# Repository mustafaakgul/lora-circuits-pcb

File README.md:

## Collection of LoRa peripheral circuits for various applications

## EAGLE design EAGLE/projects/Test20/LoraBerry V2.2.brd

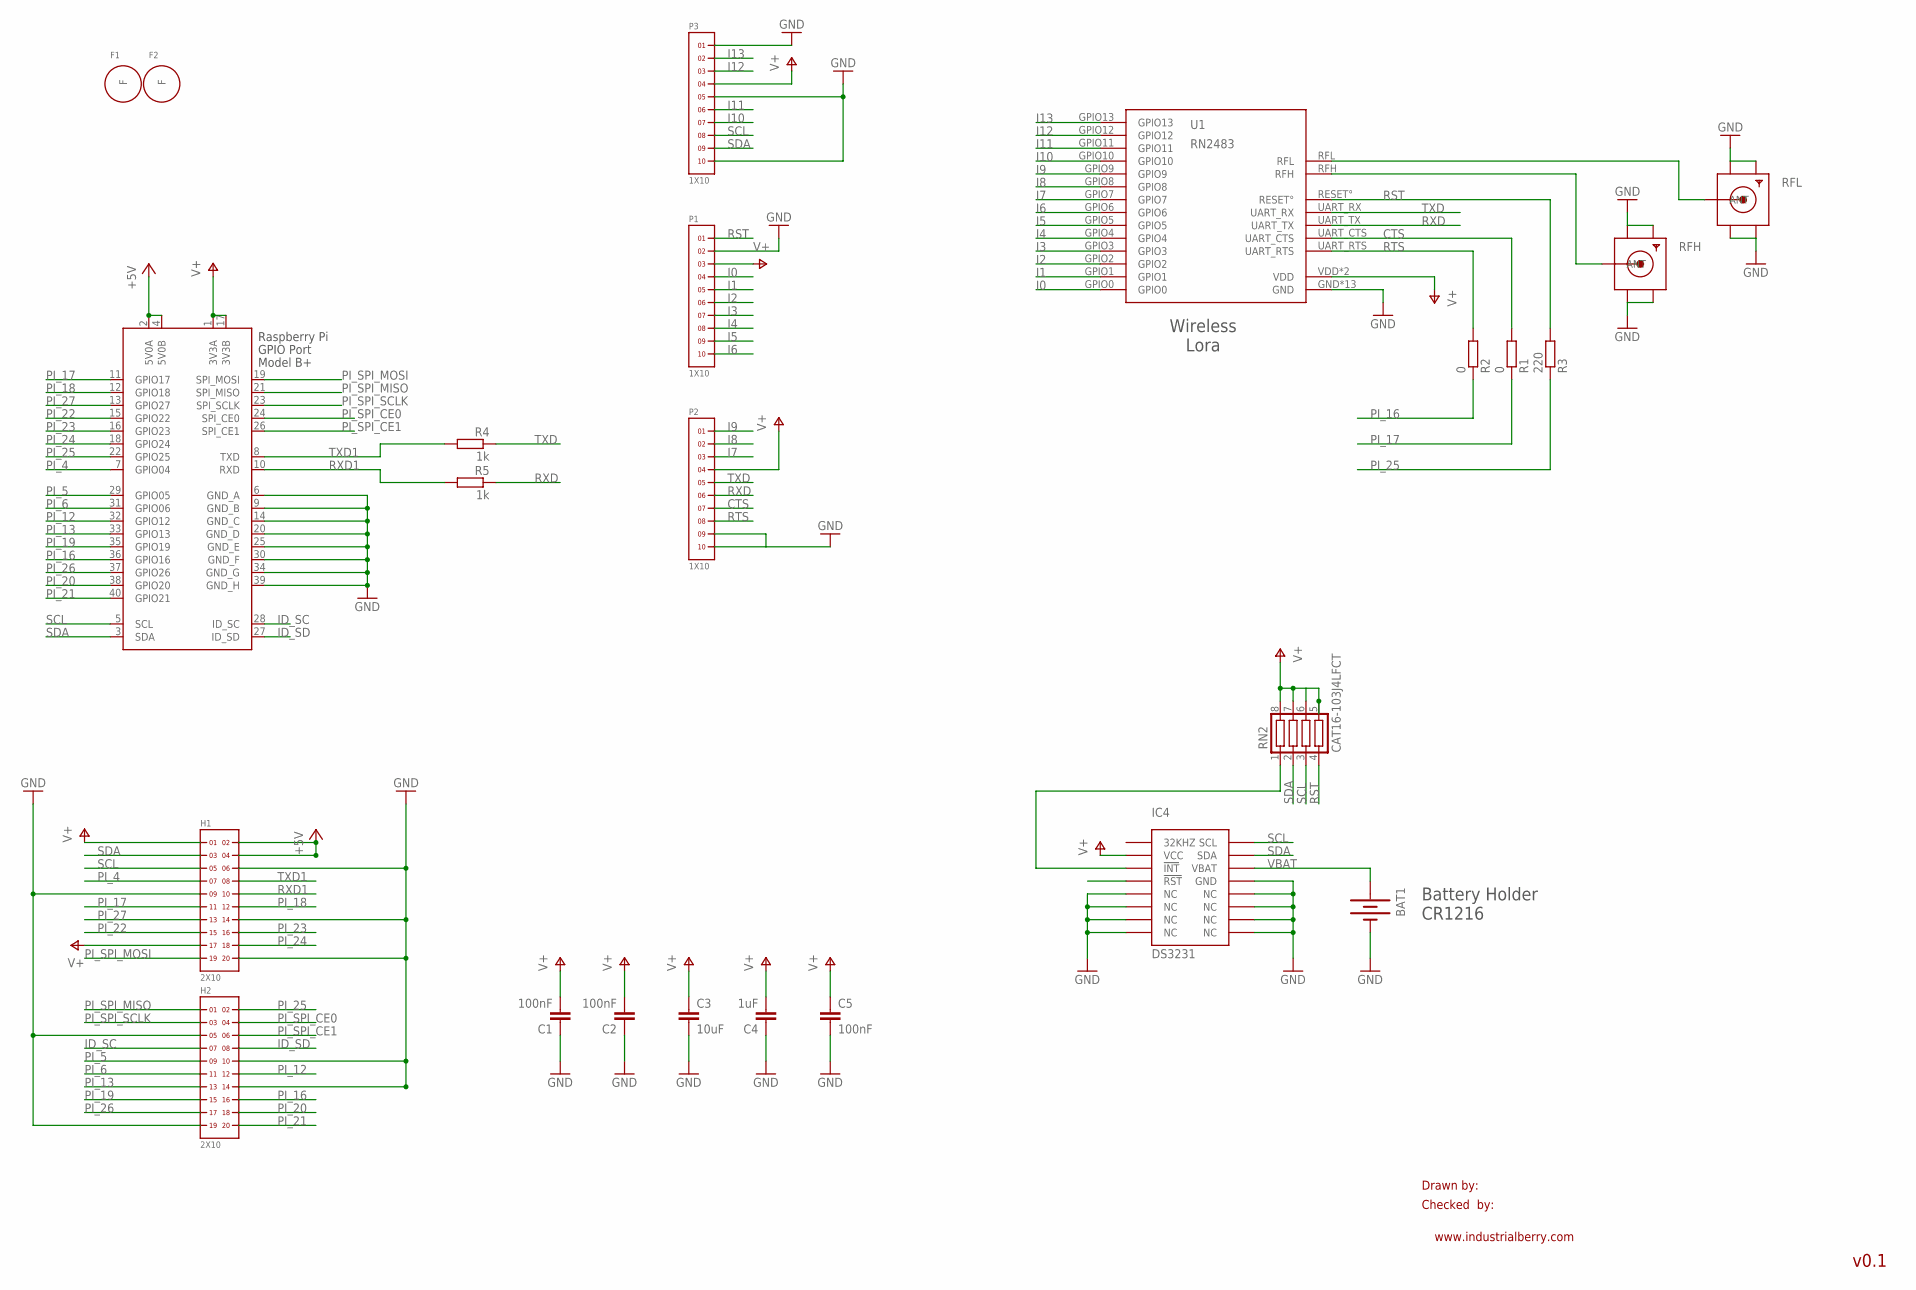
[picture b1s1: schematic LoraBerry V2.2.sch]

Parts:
BAT1: BATTERY12MM; BATTCON_12MM
C1, C2, C5: 100nF; C0603
C3: 10uF; C1206
C4: 1uF; C0603
F1, F2: FIDUCIAL-LAMINA
H1, H2: 2X10
IC4: DS3231; SOIC-16W
P1, P2, P3: 1X10
R1, R2: 0; R0603
R3: 220; R0603
R4, R5: 1k; R0603
RFH: SMACONNECTOR_EDGE; SMA_EDGELAUNCH
RFL: SMACONNECTOR_EDGE; SMA_EDGELAUNCH
RN2: CAT16-103J4LFCT; CTS742C083
RPI1: RASPBERRY_HATNODISPLAY; CONNECTOR_B+_SMT_HAT_ND
U1: RN2483

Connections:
433MHZ: RFL.P (ANT), U1.RFL
868MHZ: RFH.P (ANT), U1.RFH
+5V: H1.2, H1.4, RPI1.2 (5V0A), RPI1.4 (5V0B)
CTS: P2.7, R1.2, U1.UART_CTS
GND: BAT1.GND (-), C1.1, C2.1, C3.2, C4.1, C5.2, H1.6, H1.9, H1.14, H1.20, H2.5, H2.10, H2.14, H2.19, IC4.5 (NC), IC4.6 (NC), IC4.7 (NC), IC4.8 (NC), IC4.9 (NC), IC4.10 (NC), IC4.11 (NC), IC4.12 (NC), IC4.13 (GND), P1.2, P2.9, P2.10, P3.1, P3.5, P3.10, RFH.GND@1 (GND4), RFH.GND@2 (GND3), RFH.GND@3 (GND2), RFH.GND@4 (GND1), RFL.GND@1 (GND4), RFL.GND@2 (GND3), RFL.GND@3 (GND2), RFL.GND@4 (GND1), RPI1.6 (GND_A), RPI1.9 (GND_B), RPI1.14 (GND_C), RPI1.20 (GND_D), RPI1.25 (GND_E), RPI1.30 (GND_F), RPI1.34 (GND_G), RPI1.39 (GND_H), U1.GND, U1.GND1 (GND), U1.GND2 (GND), U1.GND3 (GND), U1.GND4 (GND), U1.GND5 (GND), U1.GND6 (GND), U1.GND7 (GND), U1.GND8 (GND), U1.GND9 (GND), U1.GND10 (GND), U1.GND11 (GND), U1.GND12 (GND)
I0: P1.4, U1.GPIO0
I1: P1.5, U1.GPIO1
I2: P1.6, U1.GPIO2
I3: P1.7, U1.GPIO3
I4: P1.8, U1.GPIO4
I5: P1.9, U1.GPIO5
I6: P1.10, U1.GPIO6
I7: P2.3, U1.GPIO7
I8: P2.2, U1.GPIO8
I9: P2.1, U1.GPIO9
I10: P3.7, U1.GPIO10
I11: P3.6, U1.GPIO11
I12: P3.3, U1.GPIO12
I13: P3.2, U1.GPIO13
ID_SC: H2.7, RPI1.28 (ID_SC)
ID_SD: H2.8, RPI1.27 (ID_SD)
unnamed: IC4.3 (!INT), RN2.1
PI_4: H1.7, RPI1.7 (GPIO04)
PI_5: H2.9, RPI1.29 (GPIO05)
PI_6: H2.11, RPI1.31 (GPIO06)
PI_12: H2.12, RPI1.32 (GPIO12)
PI_13: H2.13, RPI1.33 (GPIO13)
PI_16: H2.16, R2.1, RPI1.36 (GPIO16)
PI_17: H1.11, R1.1, RPI1.11 (GPIO17)
PI_18: H1.12, RPI1.12 (GPIO18)
PI_19: H2.15, RPI1.35 (GPIO19)
PI_20: H2.18, RPI1.38 (GPIO20)
PI_21: H2.20, RPI1.40 (GPIO21)
PI_22: H1.15, RPI1.15 (GPIO22)
PI_23: H1.16, RPI1.16 (GPIO23)
PI_24: H1.18, RPI1.18 (GPIO24)
PI_25: H2.2, R3.1, RPI1.22 (GPIO25)
PI_26: H2.17, RPI1.37 (GPIO26)
PI_27: H1.13, RPI1.13 (GPIO27)
PI_SPI_CE0: H2.4, RPI1.24 (SPI_CE0)
PI_SPI_CE1: H2.6, RPI1.26 (SPI_CE1)
PI_SPI_MISO: H2.1, RPI1.21 (SPI_MISO)
PI_SPI_MOSI: H1.19, RPI1.19 (SPI_MOSI)
PI_SPI_SCLK: H2.3, RPI1.23 (SPI_SCLK)
RST: P1.1, R3.2, RN2.4, U1.RESET°
RTS: P2.8, R2.2, U1.UART_RTS
RXD: P2.6, R5.1, U1.UART_TX
RXD1: H1.10, R5.2, RPI1.10 (RXD)
SCL: H1.5, IC4.16 (SCL), P3.8, RN2.3, RPI1.5 (SCL)
SDA: H1.3, IC4.15 (SDA), P3.9, RN2.2, RPI1.3 (SDA)
TXD: P2.5, R4.1, U1.UART_RX
TXD1: H1.8, R4.2, RPI1.8 (TXD)
V+: C1.2, C2.2, C3.1, C4.2, C5.1, H1.1, H1.17, IC4.2 (VCC), P1.3, P2.4, P3.4, RN2.5, RN2.6, RN2.7, RN2.8, RPI1.1 (3V3A), RPI1.17 (3V3B), U1.VDD, U1.VDD2 (VDD)
VBAT: BAT1.PWR@1 (+), IC4.14 (VBAT)

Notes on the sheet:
Drawn by:
Checked by:
www.industrialberry.com
v0.1
Battery Holder CR1216
Wireless Lora

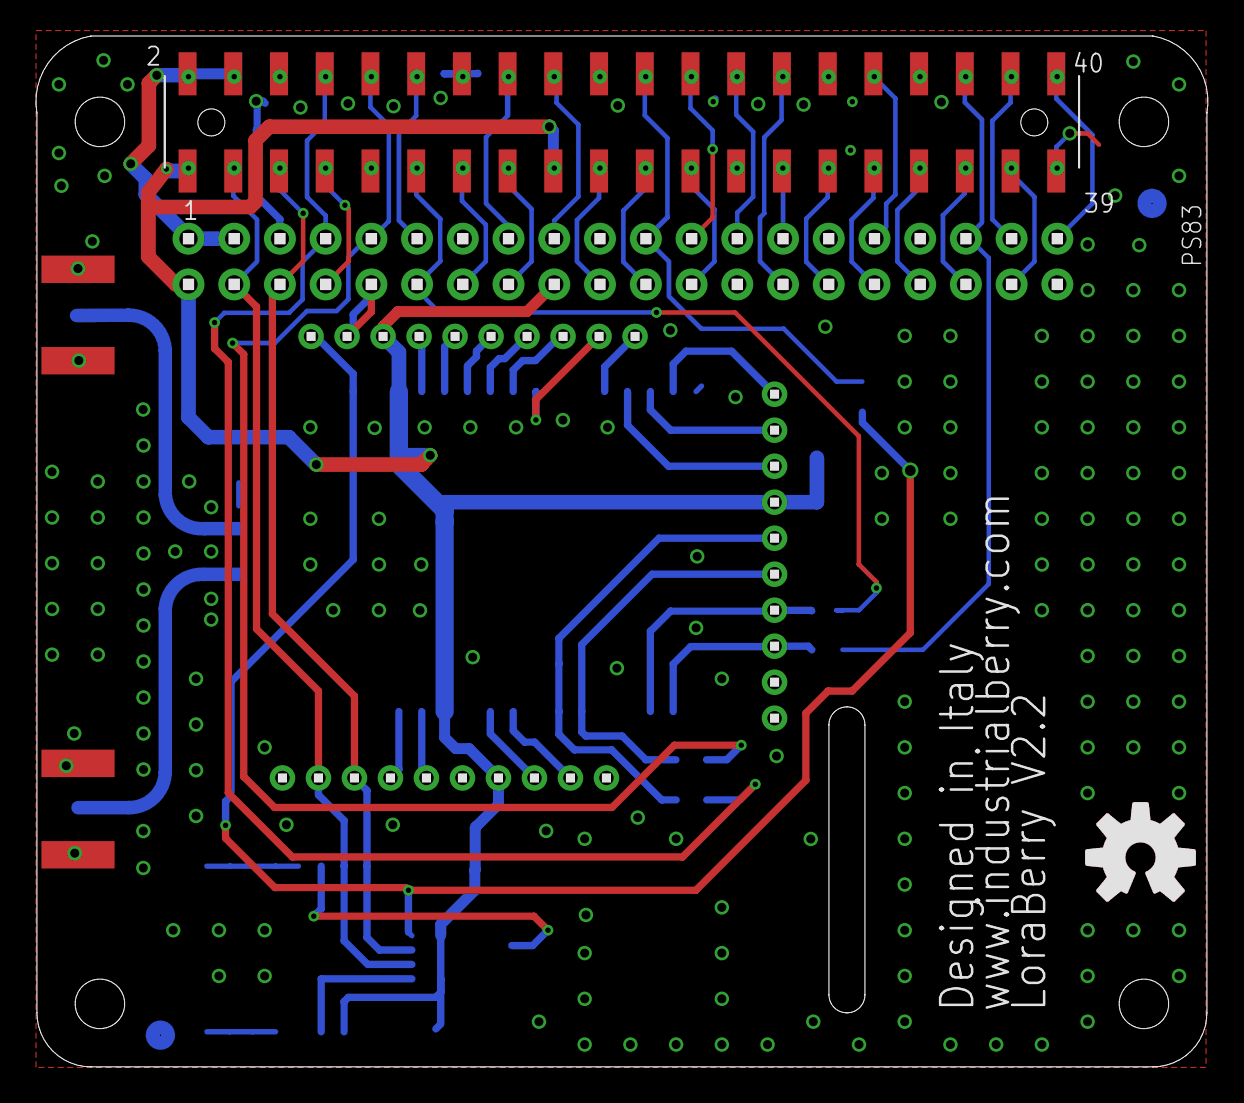
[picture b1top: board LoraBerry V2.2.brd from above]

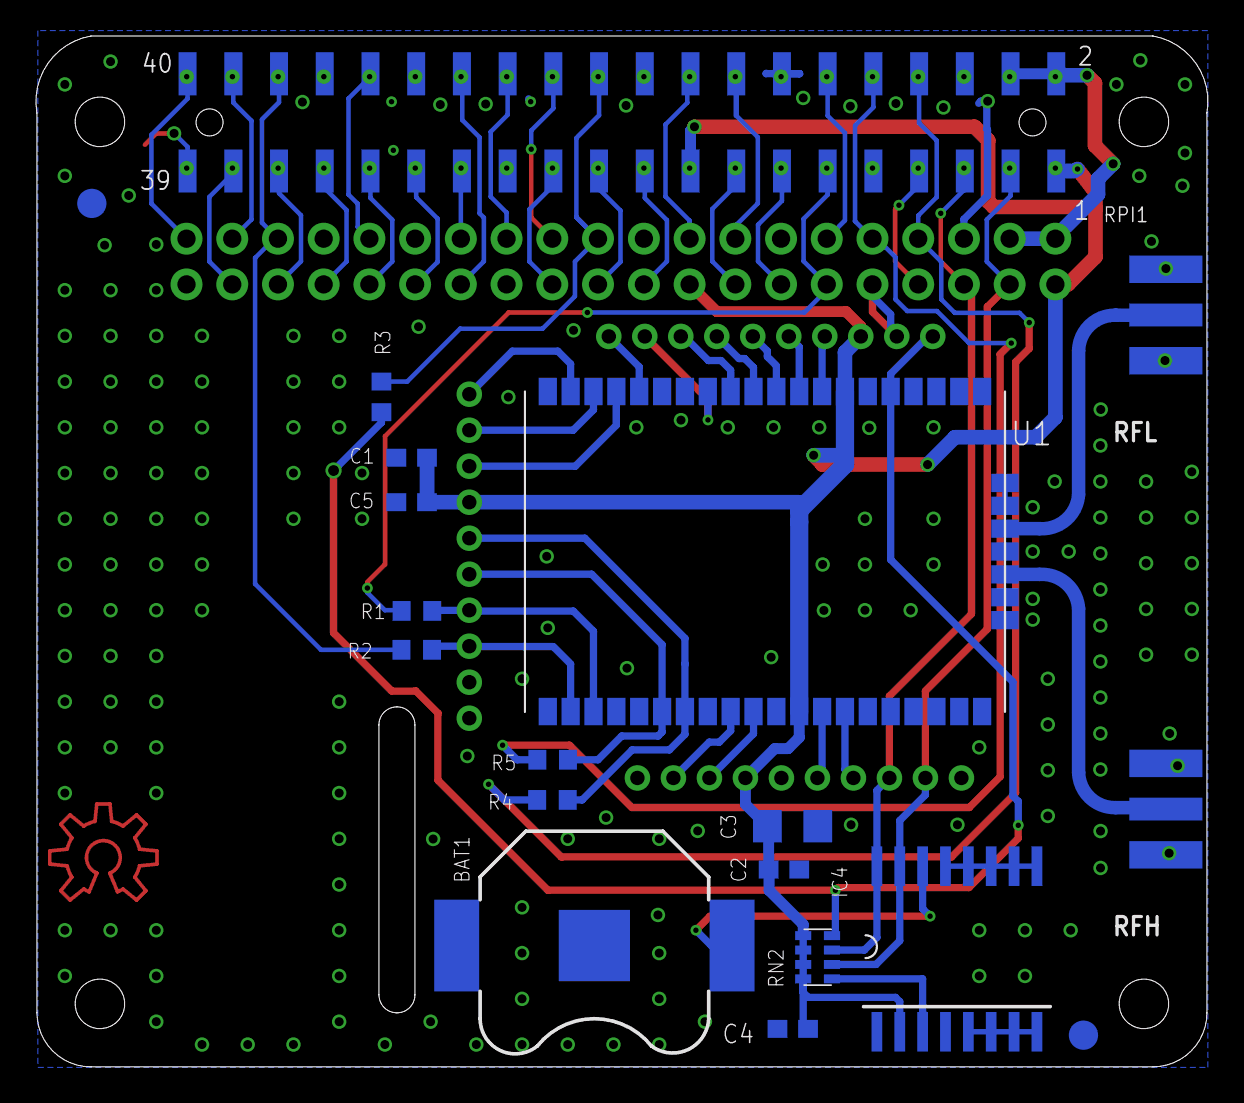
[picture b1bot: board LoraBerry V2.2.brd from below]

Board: 2 copper layers, 65.1 x 57.3 mm, 24 parts (18 on the bottom side), 54 nets.

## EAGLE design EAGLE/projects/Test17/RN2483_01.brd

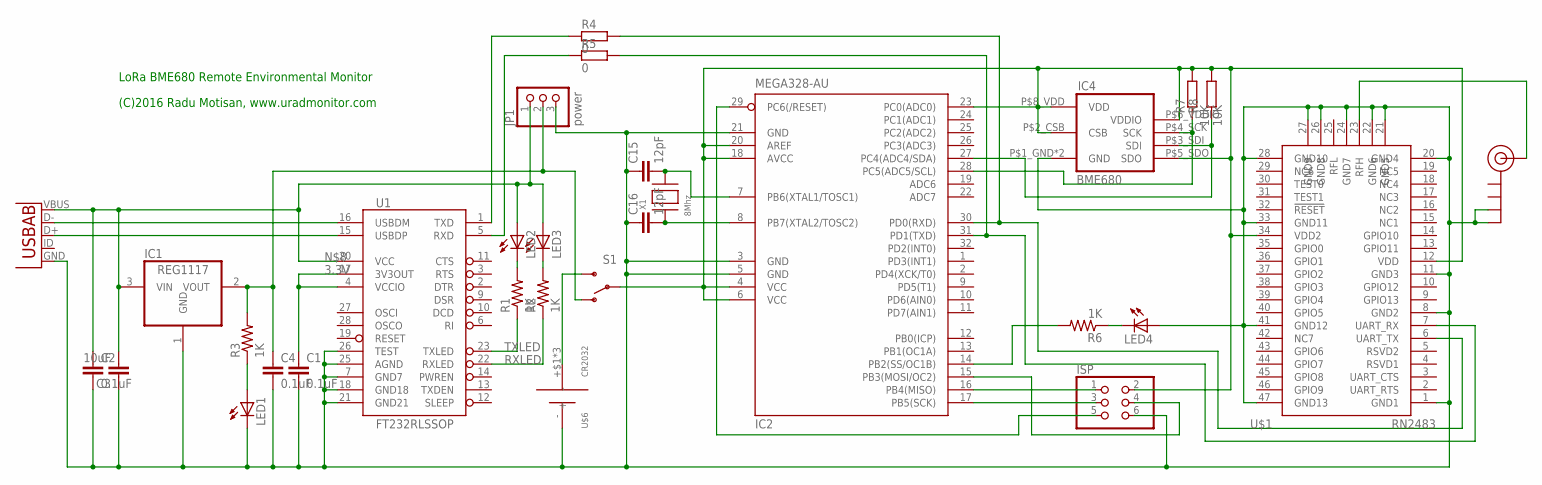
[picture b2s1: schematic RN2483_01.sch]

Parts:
C1, C2, C4: 0.1uF; 0805
C3: 10uF; C0805K
C15, C16: 12pF; C0805K
IC1: REG1117; SOT223
IC2: MEGA328-AU; TQFP32-08
IC4: BME680
ISP: PINHD-2X3; 2X03
J$1: SMA_EDGE; SMA-EDGE
JP1: power; 1X03
LED1, LED2, LED3, LED4: LEDCHIP-LED0805; CHIP-LED0805
R1, R2, R3, R6: 1K; 0805
R4, R5: 0; R0805
R7, R8: 10K; R0805
S1: SWITCH-SPDT-SMD-A; SWITCH-SPST-SMD-A
U1: FT232RLSSOP; SSOP28DB
U$1: RN2483
U$2: USB_AB; USB-AB-MICRO-SMD
U$6: CR2032
X1: 8Mhz; NX5032

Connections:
3.3V: C1.1, U1.4 (VCCIO), U1.17 (3V3OUT)
GND: C1.2, C2.2, C3.1, C4.2, C15.1, C16.1, IC1.1 (GND), IC2.3 (GND), IC2.5 (GND), IC2.21 (GND), IC4.P$1_GND (GND), IC4.P$7_GND (GND), ISP.6, J$1.GND@2 (GND), J$1.GND@3 (GND), JP1.3, LED1.C, LED4.A, U1.7 (GND7), U1.18 (GND18), U1.21 (GND21), U1.25 (AGND), U1.26 (TEST), U$1.1 (GND1), U$1.8 (GND2), U$1.11 (GND3), U$1.20 (GND4), U$1.21 (GND5), U$1.22 (GND6), U$1.24 (GND7), U$1.26 (GND8), U$1.27 (GND9), U$1.28 (GND10), U$1.33 (GND11), U$1.41 (GND12), U$1.47 (GND13), U$2.GND, U$6.-
unnamed: LED2.C, R1.2
unnamed: LED3.C, R2.2
unnamed: U1.16 (USBDM), U$2.D-
unnamed: U1.15 (USBDP), U$2.D+
unnamed: C4.1, IC1.2 (VOUT), JP1.2, R3.2, S1.1 (O)
unnamed: IC2.30 (PD0(RXD)), R4.2, U$1.6 (UART_TX)
unnamed: IC2.14 (PB2(SS/OC1B)), R6.2
unnamed: C2.1, C3.2, IC1.3 (VIN), JP1.1, LED2.A, LED3.A, U1.20 (VCC), U$2.VBUS
unnamed: R4.1, U1.1 (TXD)
unnamed: S1.3 (S), U$6.+$1 (+), U$6.+$2 (+), U$6.+$3 (+)
unnamed: IC2.16 (PB4(MISO)), ISP.1
unnamed: IC2.17 (PB5(SCK)), ISP.3
unnamed: IC2.15 (PB3(MOSI/OC2)), ISP.4
unnamed: IC2.29 (PC6(/RESET)), ISP.5
unnamed: J$1.SIG (SIGNAL), U$1.23 (RFH)
unnamed: LED4.C, R6.1
unnamed: C15.2, IC2.7 (PB6(XTAL1/TOSC1)), X1.P$2
unnamed: C16.2, IC2.8 (PB7(XTAL2/TOSC2)), X1.P$1
unnamed: R5.1, U1.5 (RXD)
unnamed: IC2.28 (PC5(ADC5/SCL)), IC4.P$4_SCK (SCK), R7.1
unnamed: IC2.27 (PC4(ADC4/SDA)), IC4.P$3_SDI (SDI), R8.1
unnamed: IC2.31 (PD1(TXD)), R5.2, U$1.7 (UART_RX)
unnamed: LED1.A, R3.1
RXLED: R2.1, U1.22 (RXLED)
TXLED: R1.1, U1.23 (TXLED)
VCC: IC2.4 (VCC), IC2.6 (VCC), IC2.18 (AVCC), IC2.20 (AREF), IC2.23 (PC0(ADC0)), IC4.P$2_CSB (CSB), IC4.P$5_SDO (SDO), IC4.P$6_VDDIO (VDDIO), IC4.P$8_VDD (VDD), ISP.2, R7.2, R8.2, S1.2, U$1.12 (VDD), U$1.34 (VDD2)

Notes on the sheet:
LoRa BME680 Remote Environmental Monitor
(C)2016 Radu Motisan, www.uradmonitor.com

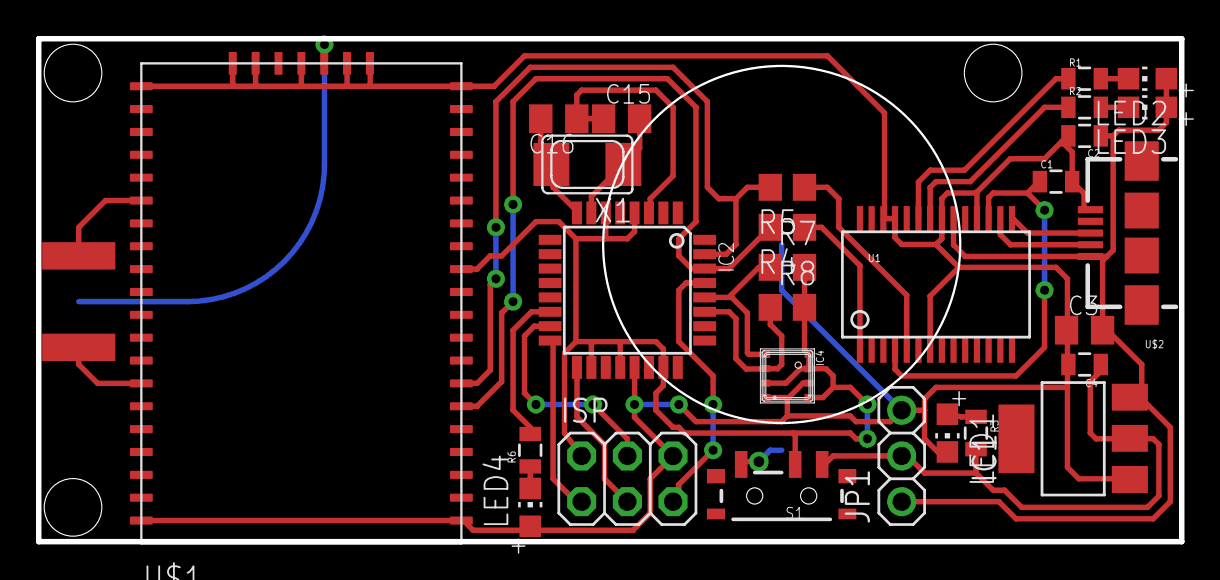
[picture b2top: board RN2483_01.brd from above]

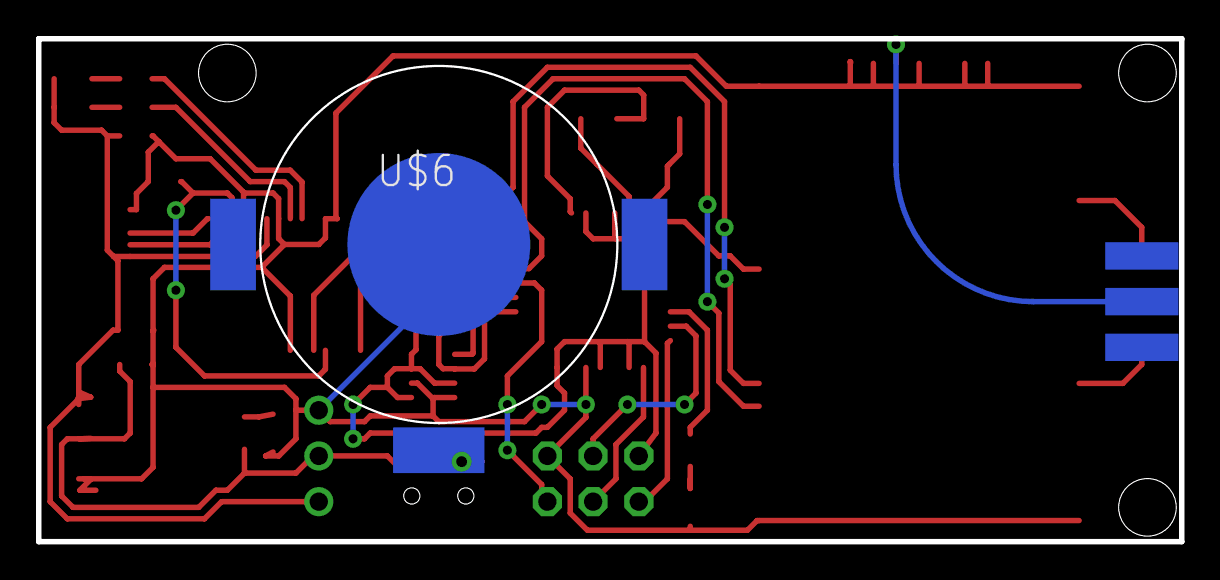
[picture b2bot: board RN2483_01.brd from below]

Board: 2 copper layers, 63.5 x 27.9 mm, 30 parts (2 on the bottom side), 28 nets.

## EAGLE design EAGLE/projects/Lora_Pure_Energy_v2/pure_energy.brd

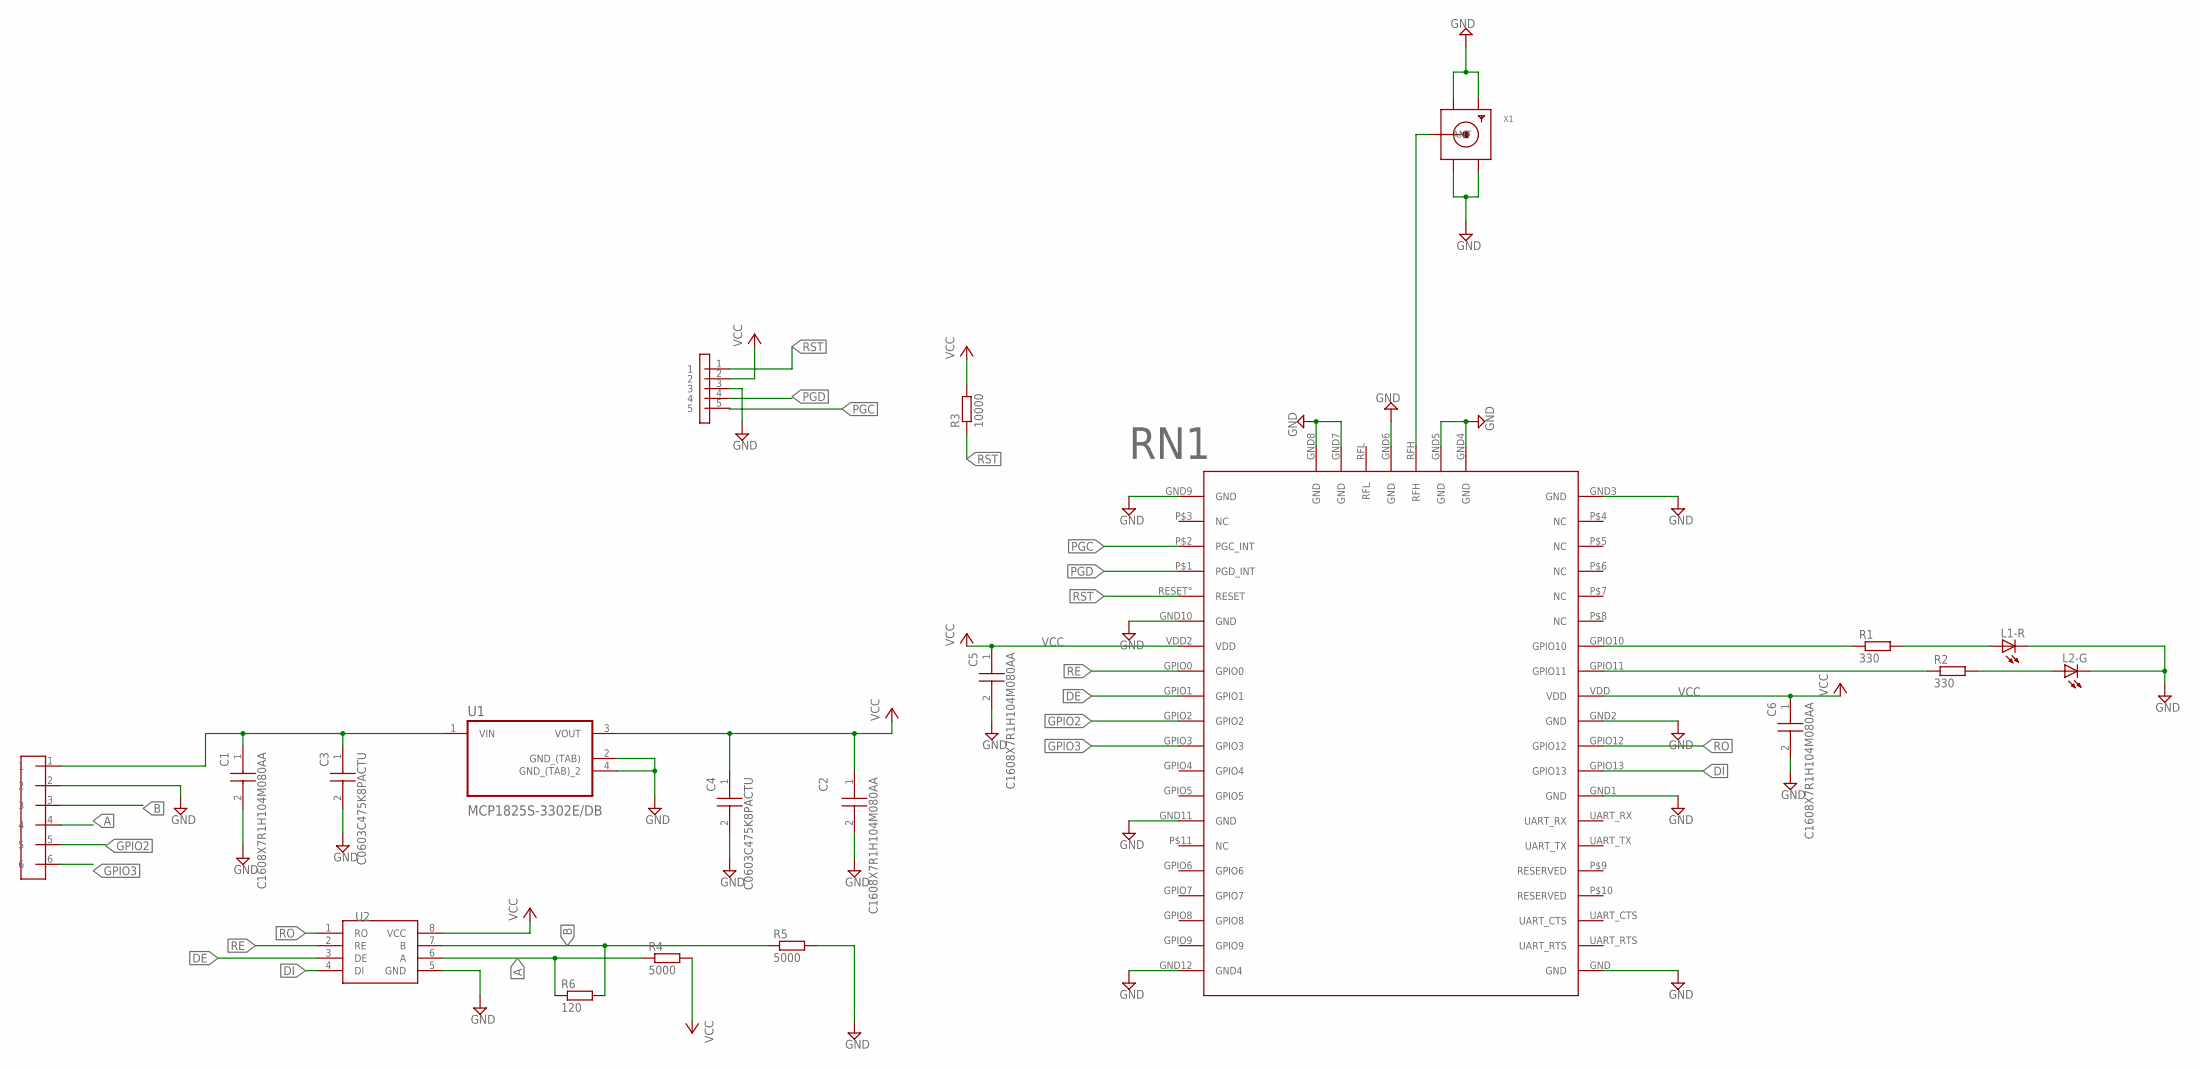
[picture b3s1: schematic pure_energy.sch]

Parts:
C1, C2, C5, C6: C1608X7R1H104M080AA; CAPC1608X80N
C3, C4: C0603C475K8PACTU; CAPC1608X85N
L1-R, L2-G: LEDCHIP-LED0603; CHIP-LED0603
R1, R2: 330; R0603
R3: 10000; R0603
R4, R5: 5000; R0805
R6: 120; R0805
RN1: NEW_RN2483
U1: MCP1825S-3302E/DB; SOT230P700X180-4N
U2: AMD3485E
U$1: CONNECTOR6_V2
U$3: ICSP_V2
X1: SMACONNECTOR_EDGE; SMA_EDGELAUNCH

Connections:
A: R4.1, R6.1, U2.6 (A), U$1.4
B: R5.1, R6.2, U2.7 (B), U$1.3
DE: RN1.GPIO1, U2.3 (DE)
DI: RN1.GPIO13, U2.4 (DI)
GND: C1.2, C2.2, C3.2 (C2), C4.2 (C2), C5.2, C6.2, L1-R.C, L2-G.C, R5.2, RN1.GND, RN1.GND1 (GND), RN1.GND2 (GND), RN1.GND3 (GND), RN1.GND4 (GND), RN1.GND5 (GND), RN1.GND6 (GND), RN1.GND7 (GND), RN1.GND8 (GND), RN1.GND9 (GND), RN1.GND10 (GND), RN1.GND11 (GND), RN1.GND12 (GND4), U1.2 (GND_(TAB)), U1.4 (GND_(TAB)_2), U2.5 (GND), U$1.2, U$3.3, X1.GND@1 (GND4), X1.GND@2 (GND3), X1.GND@3 (GND2), X1.GND@4 (GND1)
GPIO2: RN1.GPIO2, U$1.5
GPIO3: RN1.GPIO3, U$1.6
unnamed: C1.1, C3.1 (C1), U1.1 (VIN), U$1.1
unnamed: R1.1, RN1.GPIO10
unnamed: R2.1, RN1.GPIO11
unnamed: L1-R.A, R1.2
unnamed: L2-G.A, R2.2
unnamed: RN1.RFH, X1.P (ANT)
PGC: RN1.P$2 (PGC_INT), U$3.5
PGD: RN1.P$1 (PGD_INT), U$3.4
RE: RN1.GPIO0, U2.2 (RE)
RO: RN1.GPIO12, U2.1 (RO)
RST: R3.1, RN1.RESET° (RESET), U$3.1
VCC: C2.1, C4.1 (C1), C5.1, C6.1, R3.2, R4.2, RN1.VDD, RN1.VDD2 (VDD), U1.3 (VOUT), U2.8 (VCC), U$3.2

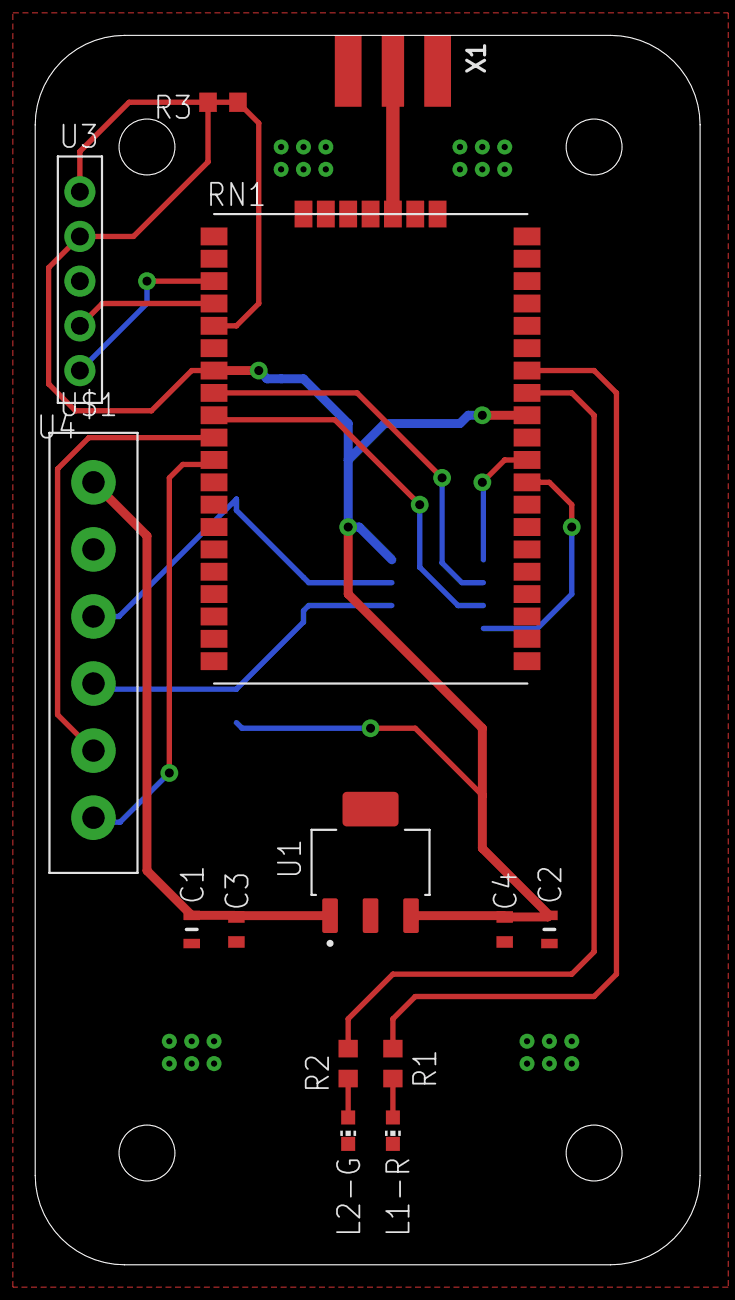
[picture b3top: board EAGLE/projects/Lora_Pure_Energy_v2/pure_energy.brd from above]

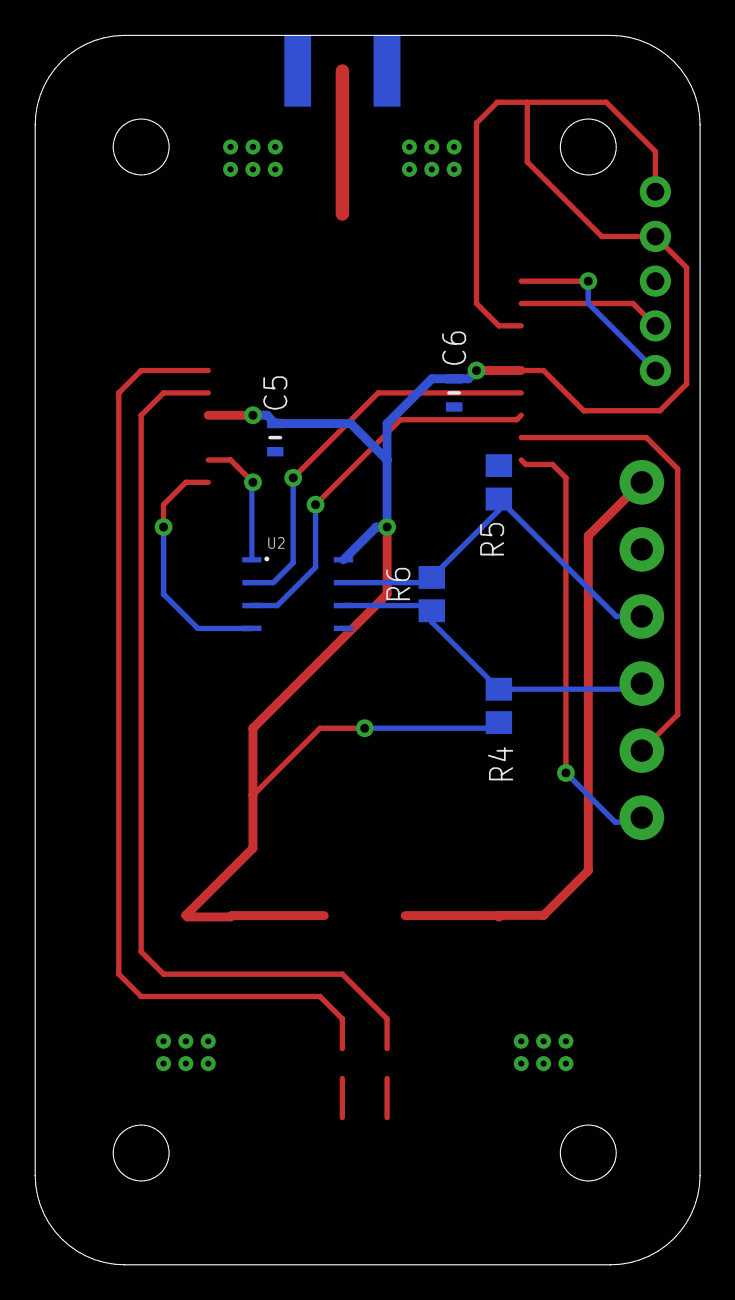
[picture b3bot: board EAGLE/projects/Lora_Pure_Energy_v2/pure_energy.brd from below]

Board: 2 copper layers, 37.8 x 69.8 mm, 20 parts (6 on the bottom side), 19 nets.

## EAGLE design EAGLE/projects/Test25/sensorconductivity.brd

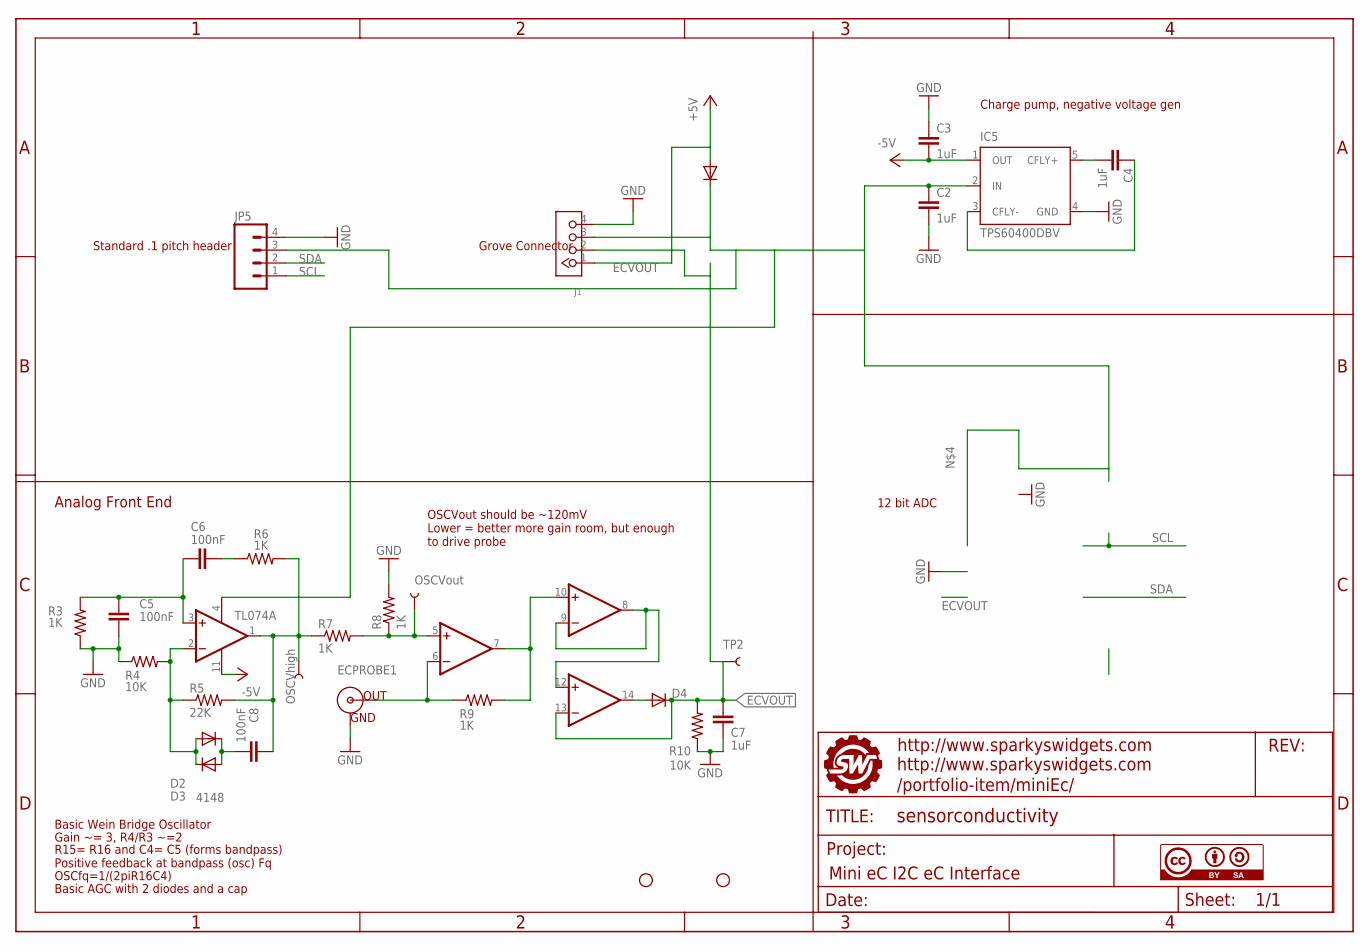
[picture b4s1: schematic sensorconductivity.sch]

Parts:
C2, C3, C4, C7: 1uF; 0805
C5, C6, C8: 100nF; 0805
D1, D2, D3: 4148; SOD123
D4: DIODE-SMB; SMB
ECPROBE1: BNCPTH; BNC
IC5: TPS60400DBV; SOT23-DBV
J1: TWIG-4P-2.0-2.0; 4P-2.0
JP1, JP3: STAND-OFF
JP5: M04PTH; 1X04
R3, R6, R7, R8, R9: 1K; 0805
R4, R10: 10K; 0805
R5: 22K; 0805
TL074: TL074; SO14
TP2: TEST-POINT3; PAD.03X.03
TP3: OSCVhigh; PAD.03X.03
TP5: OSCVout; PAD.03X.03
U$4: FRAME_MINIEC; SWPCBLOGOWITHINFO
U$5: CC-BY-SA

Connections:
+5V: D1.A, J1.1
-5V: C3.2, IC5.1 (OUT), TL074.11 (V-)
ECVOUT: C7.2, D4.C, J1.2, R10.2, TL074.13 (-IN), TP2.P$1
GND: C2.2, C3.1, C5.1, C7.1, ECPROBE1.GND, IC5.4 (GND), J1.4, JP5.4, R3.1, R4.1, R8.2, R10.1
unnamed: C8.2, D2.C, D3.A
unnamed: C2.1, D1.C, IC5.2 (IN), J1.3, JP5.3, TL074.4 (V+)
unnamed: C4.1, IC5.3 (CFLY-)
unnamed: C4.2, IC5.5 (CFLY+)
unnamed: C5.2, C6.2, R3.2, TL074.3 (+IN)
unnamed: D2.A, D3.C, R4.2, R5.1, TL074.2 (-IN)
unnamed: C6.1, R6.1
unnamed: C8.1, R5.2, R6.2, R7.1, TL074.1 (OUT), TP3.P$1
unnamed: R7.2, R8.1, TL074.5 (+IN), TP5.P$1
unnamed: ECPROBE1.S (OUT), R9.1, TL074.6 (-IN)
unnamed: R9.2, TL074.7 (OUT), TL074.10 (+IN)
unnamed: TL074.8 (OUT), TL074.9 (-IN), TL074.12 (+IN)
unnamed: D4.A, TL074.14 (OUT)
SCL: JP5.1
SDA: JP5.2

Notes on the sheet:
Grove Connector
Standard .1 pitch header
12 bit ADC
Charge pump, negative voltage gen
Analog Front End
Basic Wein Bridge Oscillator
Gain ~= 3, R4/R3 ~=2
R15= R16 and C4= C5 (forms bandpass) Positive feedback at bandpass (osc) Fq
OSCfq=1/(2piR16C4)
Basic AGC with 2 diodes and a cap
OSCVout should be ~120mV Lower = better more gain room, but enough to drive probe

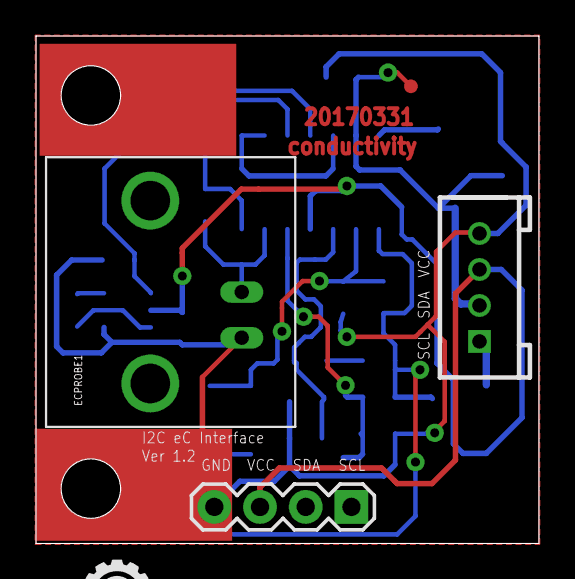
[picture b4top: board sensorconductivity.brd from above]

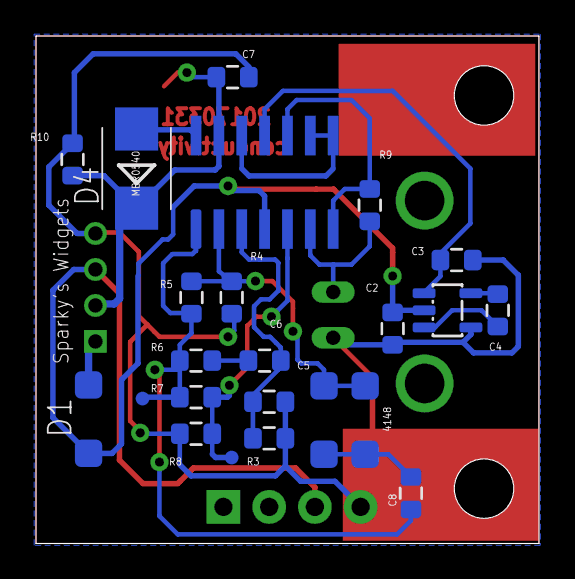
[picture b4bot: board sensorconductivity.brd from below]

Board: 2 copper layers, 27.9 x 28.2 mm, 31 parts (23 on the bottom side), 17 nets.

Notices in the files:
parts and their libraries:
SparkFun-Connectors: Licensing: Creative Commons ShareAlike 4.0 International - https://creativecommons.org/licenses/by-sa/4.0
sparkfun-connectors: Licensing: CC v3.0 Share-Alike You are welcome to use this library for commercial purposes.
